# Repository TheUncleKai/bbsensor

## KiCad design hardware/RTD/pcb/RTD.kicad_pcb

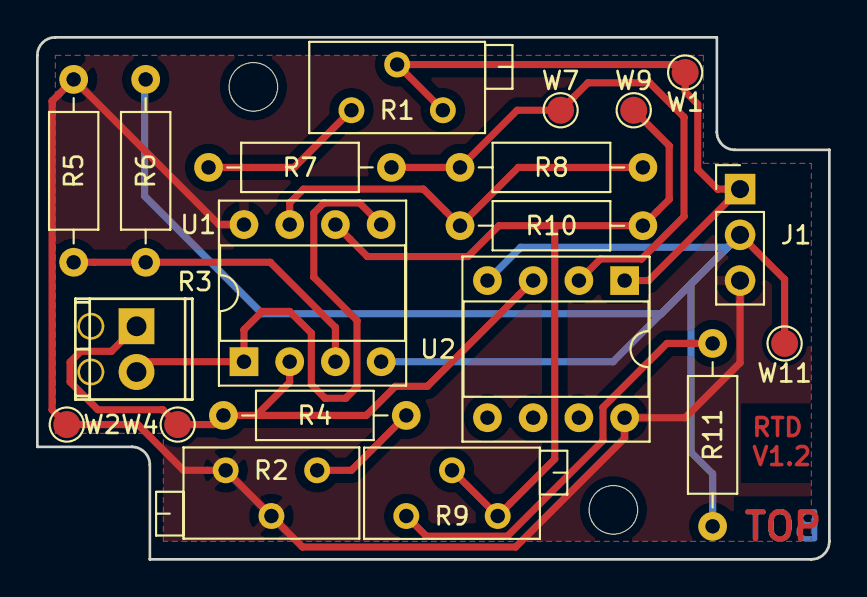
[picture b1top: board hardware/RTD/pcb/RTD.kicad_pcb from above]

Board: 2 copper layers, 44.0 x 29.0 mm, 20 parts (0 on the bottom side), 12 nets.

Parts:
J1: Conn_01x03; PinHeader_1x03_P2.54mm_Vertical
R1: 405; Potentiometer_Bourns_3296Z_Horizontal
R2: 300; Potentiometer_Bourns_3296Z_Horizontal
R3: PT100; TerminalBlock_Pheonix_MPT-2.54mm_2pol
R4: 2k2; R_Axial_DIN0207_L6.3mm_D2.5mm_P10.16mm_Horizontal
R5, R6: 10k; R_Axial_DIN0207_L6.3mm_D2.5mm_P10.16mm_Horizontal
R7: 4k7; R_Axial_DIN0207_L6.3mm_D2.5mm_P10.16mm_Horizontal
R8, R10: 200; R_Axial_DIN0207_L6.3mm_D2.5mm_P10.16mm_Horizontal
R9: 470; Potentiometer_Bourns_3296Z_Horizontal
R11: 2k; R_Axial_DIN0207_L6.3mm_D2.5mm_P10.16mm_Horizontal
U1, U2: OPA2340; DIP-8_W7.62mm_Socket
W1, W2, W4, W7, W9, W11: TestPoint_Pad_D1.5mm

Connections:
+5V: J1.3, R2.2, R2.3, R5.1, U1.8, U2.8, W2.1
/SIGNAL: J1.1, R1.2, R1.3, U2.1, W1.1
GND: J1.2, R6.1, R11.2, U1.4, U2.4, W11.1
unnamed: R1.1, R7.2
unnamed: R2.1, R4.1
unnamed: R3.1, R4.2, U1.2, U2.3, W4.1
unnamed: R3.2, U1.1, U1.5
unnamed: R5.2, R6.2, U1.3
unnamed: R7.1, R8.2, U2.2, W7.1
unnamed: R9.2, R9.3, R10.1, U1.6, W9.1
unnamed: R8.1, R10.2, U1.7
unnamed: R9.1, R11.1

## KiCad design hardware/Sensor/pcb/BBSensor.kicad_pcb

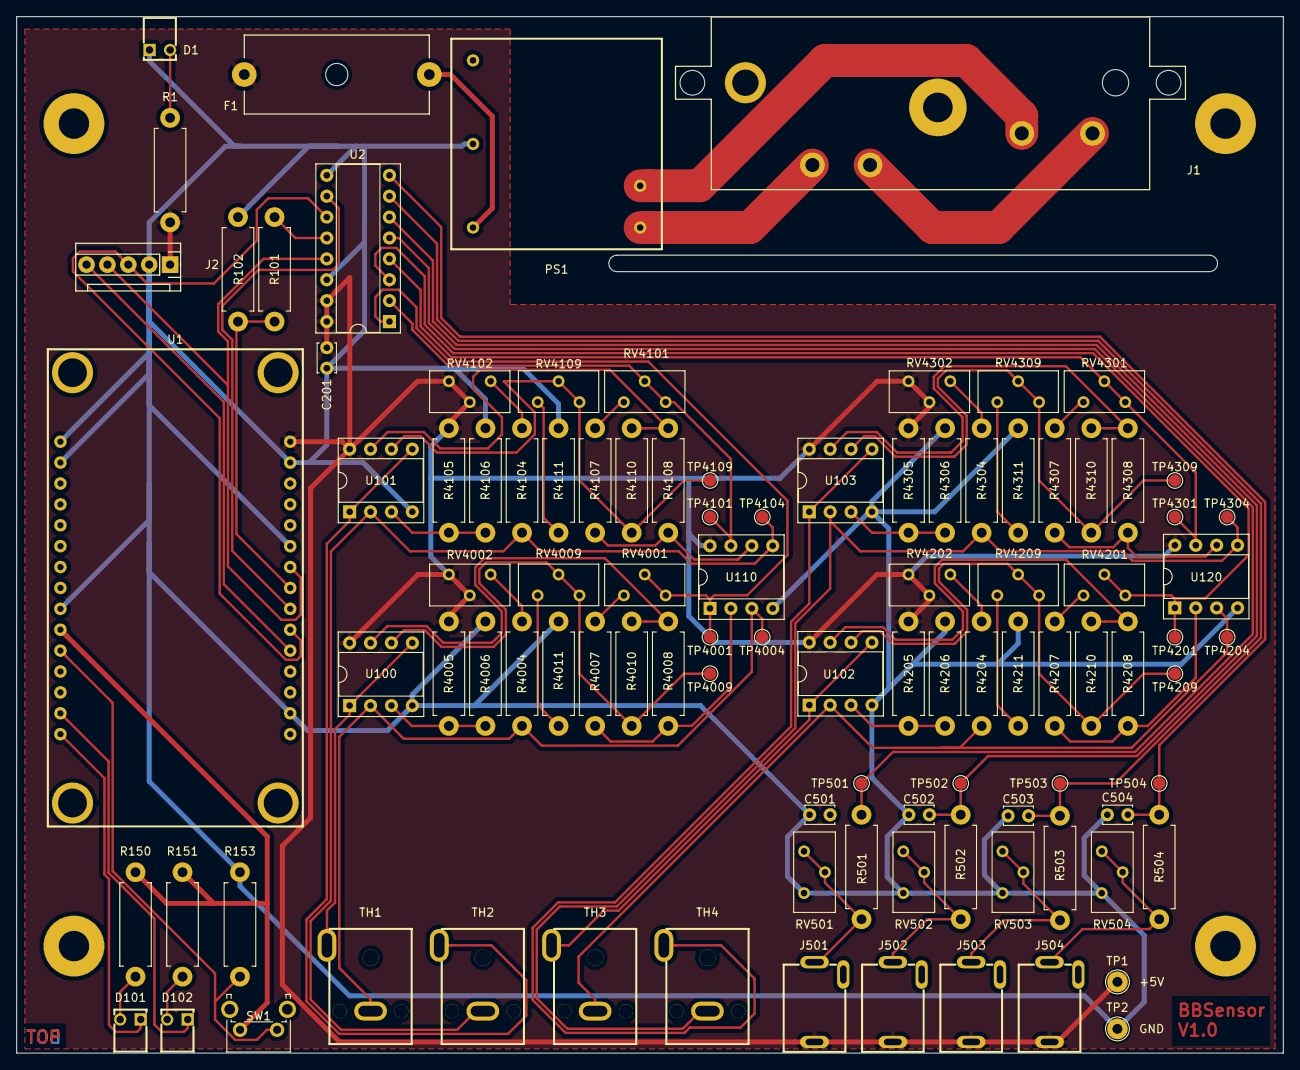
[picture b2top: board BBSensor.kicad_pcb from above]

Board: 2 copper layers, 154.0 x 126.0 mm, 101 parts (0 on the bottom side), 67 nets.

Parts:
C201, C501, C502, C503, C504: 100n; C_Disc_D3.4mm_W2.1mm_P2.50mm
D1: POWER; 5600F
D101: RED; 5600F
D102: GREEN; 5600F
F1: Fuse; Fuse_holder_20x5_22.5
J1: Schurter_CMF1; CMF1
J2: Display; Molex_KK256_Pin_Header_Straight_1x05
J501, J502, J503, J504: AudioJack2_SwitchT; LUMBERG_1501_09
PS1: TMPS_05; Traco_TMPS_05
R1: 220; R_Axial_DIN0411_L9.9mm_D3.6mm_P12.70mm_Horizontal
R101: 1k; R_Axial_DIN0411_L9.9mm_D3.6mm_P12.70mm_Horizontal
R102, R153, R4004, R4104, R4204, R4304: 2k2; R_Axial_DIN0411_L9.9mm_D3.6mm_P12.70mm_Horizontal
R150, R151: 140; R_Axial_DIN0411_L9.9mm_D3.6mm_P12.70mm_Horizontal
R501, R502, R503, R504, R4005, R4006, R4105, R4106, R4205, R4206, R4305, R4306: 10k; R_Axial_DIN0411_L9.9mm_D3.6mm_P12.70mm_Horizontal
R4007, R4107, R4207, R4307: 4k7; R_Axial_DIN0411_L9.9mm_D3.6mm_P12.70mm_Horizontal
R4008, R4010, R4108, R4110, R4208, R4210, R4308, R4310: 200; R_Axial_DIN0411_L9.9mm_D3.6mm_P12.70mm_Horizontal
R4011, R4111, R4211, R4311: 2k; R_Axial_DIN0411_L9.9mm_D3.6mm_P12.70mm_Horizontal
RV501, RV502, RV503, RV504: 10k; Potentiometer_Bourns_3296Y_Vertical
RV4001, RV4101, RV4201, RV4301: 405; Potentiometer_Bourns_3296Y_Vertical
RV4002, RV4102, RV4202, RV4302: 300; Potentiometer_Bourns_3296Y_Vertical
RV4009, RV4109, RV4209, RV4309: 470; Potentiometer_Bourns_3296Y_Vertical
SW1: SW_Push; SW_Tactile_SPST_Angled_PTS645Vx83-2LFS
TH1, TH2, TH3, TH4: Thermistor_NTC; LUMBERG_1553_02
TP1, TP2: TestPoint; TestPoint_THTPad_D2.5mm_Drill1.2mm
TP501, TP502, TP503, TP504, TP4001, TP4004, TP4009, TP4101, TP4104, TP4109, TP4201, TP4204, TP4209, TP4301, TP4304, TP4309: TestPoint; TestPoint_Pad_D1.5mm
U1: ESP8266-12E_NodeMCU_Lolin
U2: MCP3208; DIP-16_W7.62mm_Socket
U100, U101, U102, U103, U110, U120: OPA2340; DIP-8_W7.62mm_Socket

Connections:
+3V3: R150.1, R151.1, SW1.2, U1.21
+5V: C201.1, F1.1, J2.1, J501.S, J502.S, J503.S, J504.S, R1.2, R4005.2, R4105.2, R4205.2, R4305.2, RV4002.2, RV4002.3, RV4102.2, RV4102.3, RV4202.2, RV4202.3, RV4302.2, RV4302.3, TP1.1, U1.15, U2.15, U2.16, U100.8, U101.8, U102.8, U103.8, U110.8, U120.8
/Analog/Digital/SPI1: J2.3, U1.6, U2.11
/Analog/Digital/SPI2: R101.2, U2.12
/Analog/Digital/SPI3: J2.4, U1.9, U2.13
/Analog/Digital/SPI4: U1.7, U2.10
/Analog/Digital/TEMP1: RV4001.2, RV4001.3, TP4001.1, U2.1, U110.1
/Analog/Digital/TEMP2: RV4101.2, RV4101.3, TP4101.1, U2.2, U110.7
/Analog/Digital/TEMP3: RV4201.2, RV4201.3, TP4201.1, U2.3, U120.1
/Analog/Digital/TEMP4: RV4301.2, RV4301.3, TP4301.1, U2.4, U120.7
/Analog/Digital/TEMP5: C501.1, R501.1, TP501.1, U2.5
/Analog/Digital/TEMP6: C502.1, R502.1, TP502.1, U2.6
/Analog/Digital/TEMP7: C503.1, R503.1, TP503.1, U2.7
/Analog/Digital/TEMP8: C504.1, R504.1, TP504.1, U2.8
/Display/SPI5: J2.5, U1.5
/ESP8266/MISO: R101.1, R102.1, U1.8
GND: C201.2, C501.2, C502.2, C503.2, C504.2, D1.1, J2.2, PS1.4, R102.2, R153.2, R4006.1, R4011.2, R4106.1, R4111.2, R4206.1, R4211.2, R4306.1, R4311.2, RV501.3, RV502.3, RV503.3, RV504.3, TP2.1, U1.2, U1.10, U1.14, U1.22, U1.29, U1.30, U2.9, U2.14, U100.4, U101.4, U102.4, U103.4, U110.4, U120.4
unnamed: D1.2, R1.1
unnamed: D101.1, U1.16
unnamed: D101.2, R150.2
unnamed: D102.1, U1.17
unnamed: D102.2, R151.2
unnamed: F1.2, PS1.5
unnamed: J1.1, PS1.2
unnamed: J1.2, J1.4
unnamed: J1.3, PS1.1
unnamed: J501.T, R501.2, RV501.1, RV501.2
unnamed: J502.T, R502.2, RV502.1, RV502.2
unnamed: J503.T, R503.2, RV503.1, RV503.2
unnamed: J504.T, R504.2, RV504.1, RV504.2
unnamed: R153.1, SW1.1, U1.20
unnamed: R4004.1, TH1.2, TP4004.1, U100.2, U110.3
unnamed: R4004.2, RV4002.1
unnamed: R4005.1, R4006.2, U100.3
unnamed: R4007.1, RV4001.1
unnamed: R4007.2, R4008.1, U110.2
unnamed: R4008.2, R4010.1, U100.7
unnamed: R4010.2, RV4009.2, RV4009.3, TP4009.1, U100.6
unnamed: R4011.1, RV4009.1
unnamed: R4104.1, TH2.2, TP4104.1, U101.2, U110.5
unnamed: R4104.2, RV4102.1
unnamed: R4105.1, R4106.2, U101.3
unnamed: R4107.1, RV4101.1
unnamed: R4107.2, R4108.1, U110.6
unnamed: R4108.2, R4110.1, U101.7
unnamed: R4110.2, RV4109.2, RV4109.3, TP4109.1, U101.6
unnamed: R4111.1, RV4109.1
unnamed: R4204.1, TH3.2, TP4204.1, U102.2, U120.3
unnamed: R4204.2, RV4202.1
unnamed: R4205.1, R4206.2, U102.3
unnamed: R4207.1, RV4201.1
unnamed: R4207.2, R4208.1, U120.2
unnamed: R4208.2, R4210.1, U102.7
unnamed: R4210.2, RV4209.2, RV4209.3, TP4209.1, U102.6
unnamed: R4211.1, RV4209.1
unnamed: R4304.1, TH4.2, TP4304.1, U103.2, U120.5
unnamed: R4304.2, RV4302.1
unnamed: R4305.1, R4306.2, U103.3
unnamed: R4307.1, RV4301.1
unnamed: R4307.2, R4308.1, U120.6
unnamed: R4308.2, R4310.1, U103.7
unnamed: R4310.2, RV4309.2, RV4309.3, TP4309.1, U103.6
unnamed: R4311.1, RV4309.1
unnamed: TH1.1, U100.1, U100.5
unnamed: TH2.1, U101.1, U101.5
unnamed: TH3.1, U102.1, U102.5
unnamed: TH4.1, U103.1, U103.5

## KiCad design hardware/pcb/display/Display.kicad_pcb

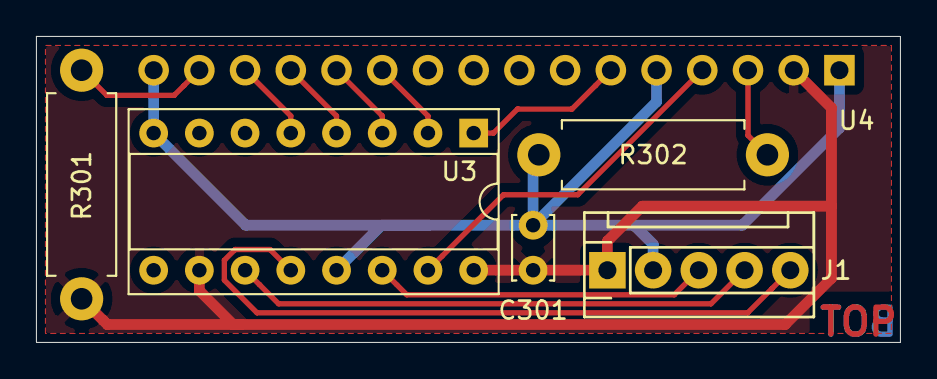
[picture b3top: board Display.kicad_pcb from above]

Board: 2 copper layers, 48.0 x 17.0 mm, 6 parts (1 on the bottom side), 13 nets.

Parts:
C301: 100n; C_Disc_D3.4mm_W2.1mm_P2.50mm
J1: Conn_01x05; Molex_KK256_Pin_Header_Straight_1x05
R301: 220; R_Axial_DIN0411_L9.9mm_D3.6mm_P12.70mm_Horizontal
R302: 2k; R_Axial_DIN0411_L9.9mm_D3.6mm_P12.70mm_Horizontal
U3: 74HC595; DIP-16_W7.62mm_Socket
U4: HD44780; PinSocket_1x16_P2.54mm_Vertical

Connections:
+5V: C301.1, J1.1, R301.1, U3.10, U3.16, U4.2
/CS2: J1.5, U3.12
/DB4: U3.2, U4.11
/DB5: U3.3, U4.12
/DB6: U3.4, U4.13
/DB7: U3.5, U4.14
/ENABLE: U3.1, U4.6
/MOSI: J1.3, U3.14
/RS: U3.15, U4.4
/SCLK: J1.4, U3.11
GND: C301.2, J1.2, R302.2, U3.8, U3.13, U4.1, U4.5, U4.16
unnamed: R301.2, U4.15
unnamed: R302.1, U4.3

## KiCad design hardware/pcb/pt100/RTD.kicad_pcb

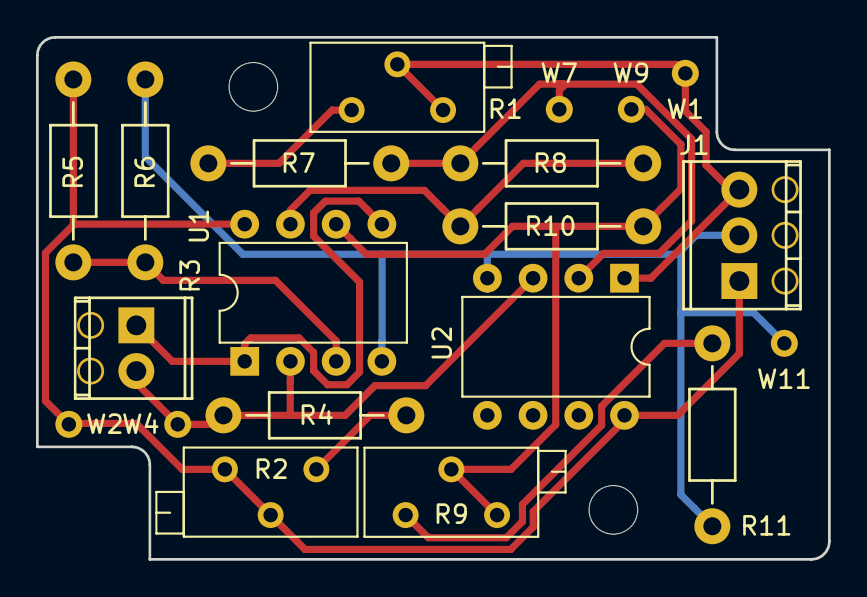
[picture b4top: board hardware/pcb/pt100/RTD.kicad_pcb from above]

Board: 2 copper layers, 44.0 x 29.0 mm, 20 parts (0 on the bottom side), 12 nets.

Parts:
J1: JACK_TRS_3PINS; TerminalBlock_Pheonix_MPT-2.54mm_3pol
R1: 405; Potentiometer_Trimmer_Bourns_3296Z
R2: 300; Potentiometer_Trimmer_Bourns_3296Z
R3: THERMISTOR; TerminalBlock_Pheonix_MPT-2.54mm_2pol
R4: 2k2; Resistor_Horizontal_RM10mm
R5, R6: 10k; Resistor_Horizontal_RM10mm
R7: 4k7; Resistor_Horizontal_RM10mm
R8, R10: 200; Resistor_Horizontal_RM10mm
R9: 470; Potentiometer_Trimmer_Bourns_3296Z
R11: 2k; Resistor_Horizontal_RM10mm
U1, U2: OPA2340; DIP-8_W7.62mm
W1: TEST_1P; Measurement_Point_Round-TH_Small
W2: TEST_2P; Measurement_Point_Round-TH_Small
W4: TEST_4P; Measurement_Point_Round-TH_Small
W7: TEST_7P; Measurement_Point_Round-TH_Small
W9: TEST_9P; Measurement_Point_Round-TH_Small
W11: TEST_11P; Measurement_Point_Round-TH_Small

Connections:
+5V: J1.1, R2.2, R2.3, R5.2, U1.8, U2.8, W2.1
/SIGNAL_T1: J1.3, R1.2, R1.3, U2.1, W1.1
AGND: J1.2, R6.1, R11.1, U1.4, U2.4, W11.1
unnamed: R1.1, R7.2
unnamed: R2.1, R4.2
unnamed: R3.1, U1.1, U1.5
unnamed: R3.2, R4.1, U1.2, U2.3, W4.1
unnamed: R5.1, R6.2, U1.3
unnamed: R7.1, R8.2, U2.2, W7.1
unnamed: R9.2, R9.3, R10.1, U1.6, W9.1
unnamed: R8.1, R10.2, U1.7
unnamed: R9.1, R11.2

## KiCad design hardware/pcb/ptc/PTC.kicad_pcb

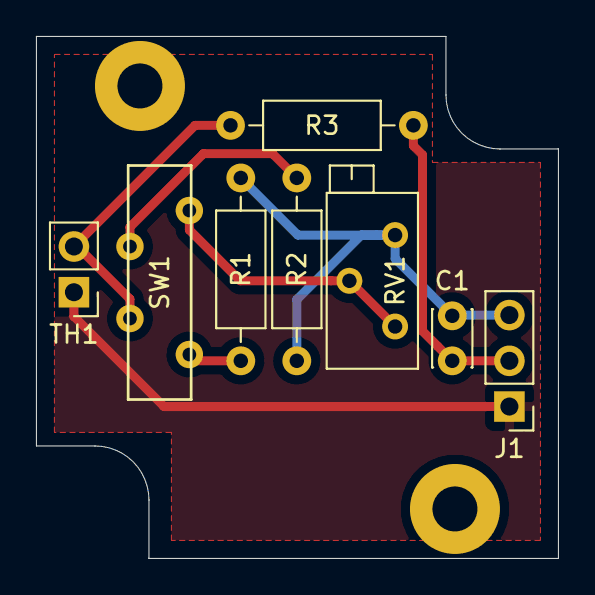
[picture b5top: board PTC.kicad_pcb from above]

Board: 2 copper layers, 29.0 x 29.0 mm, 8 parts (0 on the bottom side), 7 nets.

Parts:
C1: 100; C_Disc_D3.0mm_W2.0mm_P2.50mm
J1: Conn_01x03; PinHeader_1x03_P2.54mm_Vertical
R1, R3: 10k; R_Axial_DIN0207_L6.3mm_D2.5mm_P10.16mm_Horizontal
R2: 100k; R_Axial_DIN0207_L6.3mm_D2.5mm_P10.16mm_Horizontal
RV1: 10k; Potentiometer_Bourns_3296Z_Horizontal
SW1: SW_SP3T; ALPS_SSSS211900
TH1: Thermistor_PTC; PinHeader_1x02_P2.54mm_Vertical

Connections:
+5V: J1.1, TH1.1
GND: C1.2, J1.3, R1.2, R2.2, RV1.3
unnamed: C1.1, J1.2, R3.2
unnamed: R1.1, SW1.4
unnamed: R2.1, SW1.2
unnamed: R3.1, SW1.3, TH1.2
unnamed: RV1.1, RV1.2, SW1.1
